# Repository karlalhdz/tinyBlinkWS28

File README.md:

# tinyBlinkWS28
Proyecto para aprendizaje de eagle basico

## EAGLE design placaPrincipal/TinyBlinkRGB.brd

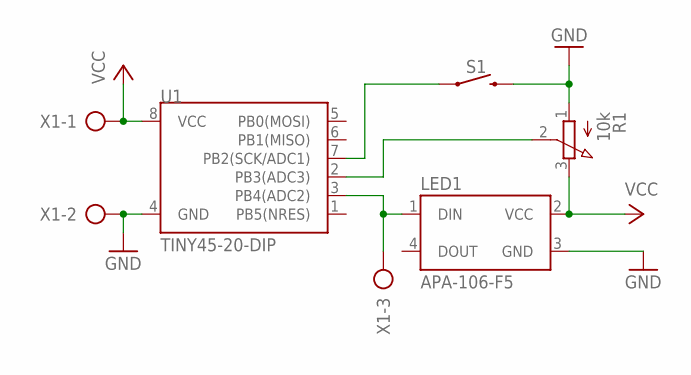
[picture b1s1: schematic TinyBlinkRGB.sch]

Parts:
LED1: APA-106-F5
R1: 10k; 3RP/1610N
S1: MOMENTARY-SWITCH-SPST-PTH-6.0MM; TACTILE_SWITCH_PTH_6.0MM
U1: TINY45-20-DIP; DIP08_MCU
X1: AK500/3

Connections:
GND: LED1.3 (GND), R1.1 (A), S1.3 (2), U1.4 (GND), X1.2
unnamed: LED1.1 (DIN), U1.3 (PB4(ADC2)), X1.3
unnamed: R1.2 (S), U1.2 (PB3(ADC3))
unnamed: S1.1, U1.7 (PB2(SCK/ADC1))
VCC: LED1.2 (VCC), R1.3 (E), U1.8 (VCC), X1.1

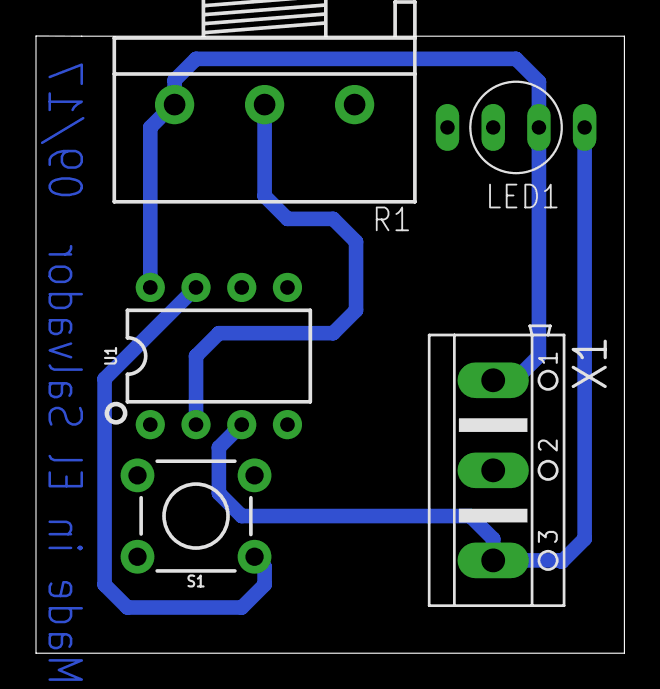
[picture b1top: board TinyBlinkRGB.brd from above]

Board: 2 copper layers, 32.7 x 34.3 mm, 5 parts (0 on the bottom side), 5 nets.

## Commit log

2017-09-24 Primera version de la tarjeta

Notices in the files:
parts and their libraries:
SparkFun-Switches: Licensing: Creative Commons ShareAlike 4.0 International - https://creativecommons.org/licenses/by-sa/4.0
